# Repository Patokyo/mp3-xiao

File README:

##An mp3 player using a Seeed Studio Xiao Esp32-S3 microcontroller

#Components:
Seeed Studio Xiao Esp32-S3
DAC Decoder with 3.5mm jack - PCM5102A
Micro-SD card reader module
OLED display - 1.5 inch, 128x128, SH1107, 4 pin
Rotary encoder with push button

#--UI--
##Modes:
Playing(folder, mode) - plays songs in the folder using the mode given, e.g. shuffle, straight
Playlist/Album select - option between playlist/album, then displays all the playlists/albums on the sd card

###Playing: mode 0
OLED display - current folder, currently playing song, progress bar, rewind, skip & play controls.
Rotary encoder - Rotate for volume, press to pause, double press to skip, press and rotate back to rewind, press and rotate forward to enter playlist/album select

###Playlist/Album select: mode 1
OLED display - displays folders/files in current directory, e.g. Playlists/Albums to start, then shows all Playlist files or Album folders
Rotary encoder - Rotate to browse folders/files, press to select

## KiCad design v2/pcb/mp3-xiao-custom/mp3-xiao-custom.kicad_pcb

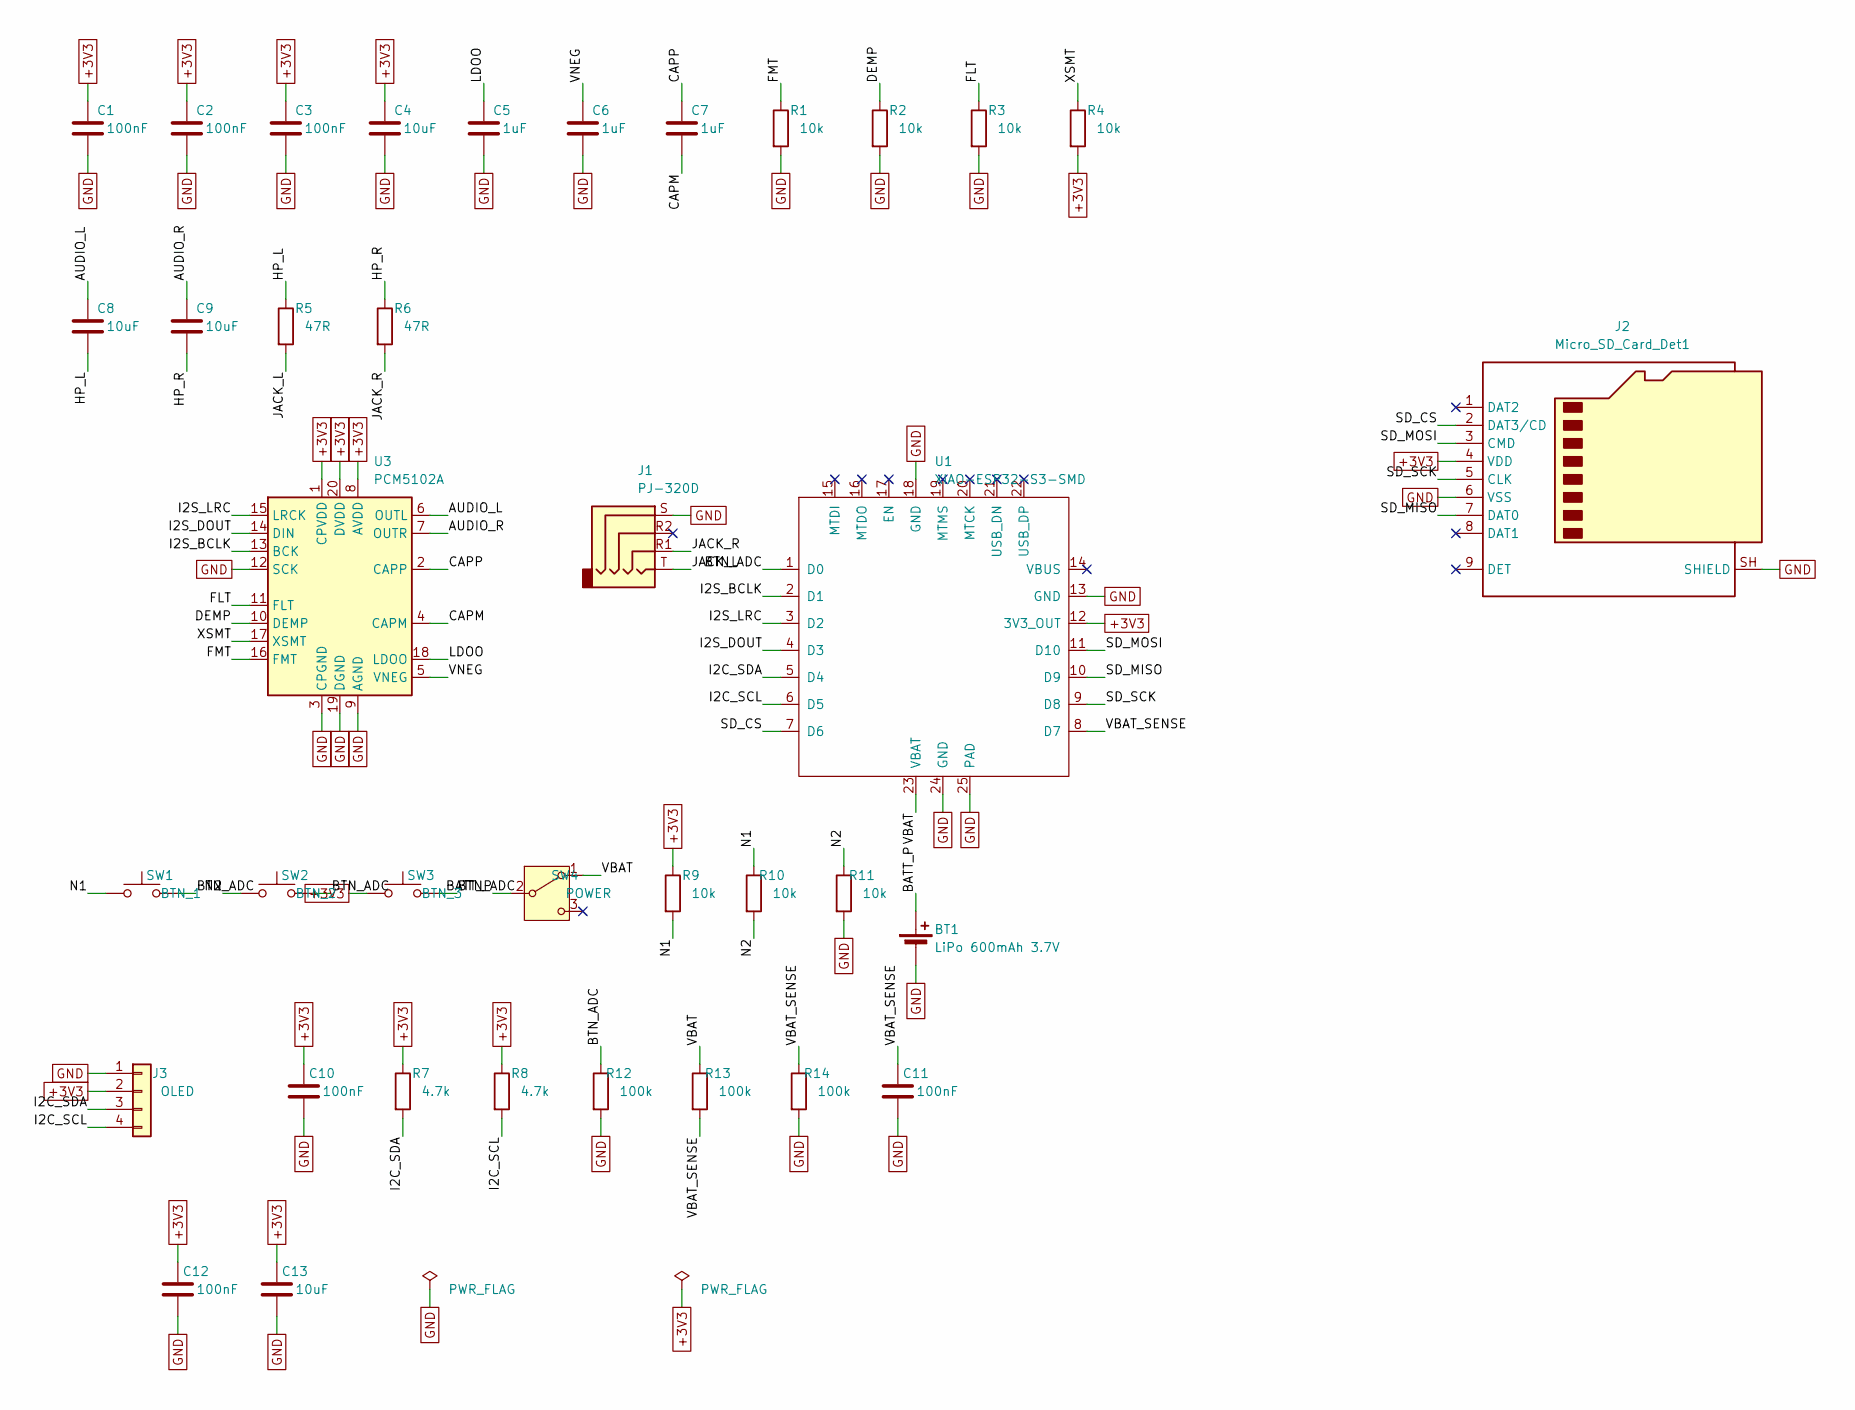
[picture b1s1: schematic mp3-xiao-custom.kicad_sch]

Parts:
BT1: LiPo 600mAh 3.7V; JST_PH_S2B-PH-K_1x02_P2.00mm_Horizontal
C1, C2, C3, C10, C11, C12: 100nF; C_0805_2012Metric_Pad1.18x1.45mm_HandSolder
C4, C8, C9, C13: 10uF; C_0805_2012Metric_Pad1.18x1.45mm_HandSolder
C5, C6, C7: 1uF; C_0805_2012Metric_Pad1.18x1.45mm_HandSolder
J1: PJ-320D; Jack_3.5mm_KoreanHropartsElec_PJ-320D-4A_Horizontal
J2: Micro_SD_Card_Det1; microSD_TF_9P_14.48x13.8mm_SMD
J3: OLED; ER_OLEDM0.91_1x-I2C
R1, R2, R3, R4, R9, R10, R11: 10k; R_0805_2012Metric_Pad1.20x1.40mm_HandSolder
R5, R6: 47R; R_0805_2012Metric_Pad1.20x1.40mm_HandSolder
R7, R8: 4.7k; R_0805_2012Metric_Pad1.20x1.40mm_HandSolder
R12, R13, R14: 100k; R_0805_2012Metric_Pad1.20x1.40mm_HandSolder
SW1: BTN_1; SW_SPST_TL3342
SW2: BTN_2; SW_SPST_TL3342
SW3: BTN_3; SW_SPST_TL3342
SW4: POWER; SW_SPDT_Shouhan_MSK12C02
U1: XIAO-ESP32-S3-SMD
U3: PCM5102A; TSSOP-20_4.4x6.5mm_P0.65mm

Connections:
+3V3: C1.1, C2.1, C3.1, C4.1, C10.1, C12.1, C13.1, J2.4 (VDD), J3.2, R4.2, R7.1, R8.1, R9.1, SW3.1, U1.12 (3V3_OUT), U3.1 (CPVDD), U3.8 (AVDD), U3.20 (DVDD)
/AUDIO_L: C8.1, U3.6 (OUTL)
/AUDIO_R: C9.1, U3.7 (OUTR)
/BATT_P: BT1.1 (+), SW4.2 (B)
/BTN_ADC: R12.1, SW1.2, SW2.2, SW3.2, U1.1 (D0)
/CAPM: C7.2, U3.4 (CAPM)
/CAPP: C7.1, U3.2 (CAPP)
/DEMP: R2.1, U3.10 (DEMP)
/FLT: R3.1, U3.11 (FLT)
/FMT: R1.1, U3.16 (FMT)
/HP_L: C8.2, R5.1
/HP_R: C9.2, R6.1
/I2C_SCL: J3.4, R8.2, U1.6 (D5)
/I2C_SDA: J3.3, R7.2, U1.5 (D4)
/I2S_BCLK: U1.2 (D1), U3.13 (BCK)
/I2S_DOUT: U1.4 (D3), U3.14 (DIN)
/I2S_LRC: U1.3 (D2), U3.15 (LRCK)
/JACK_L: J1.T, R5.2
/JACK_R: J1.R1, R6.2
/LDOO: C5.1, U3.18 (LDOO)
/N1: R9.2, R10.1, SW1.1
/N2: R10.2, R11.1, SW2.1
/SD_CS: J2.2 (DAT3/CD), U1.7 (D6)
/SD_MISO: J2.7 (DAT0), U1.10 (D9)
/SD_MOSI: J2.3 (CMD), U1.11 (D10)
/SD_SCK: J2.5 (CLK), U1.9 (D8)
/VBAT: R13.1, SW4.1 (A), U1.23 (VBAT)
/VBAT_SENSE: C11.1, R13.2, R14.1, U1.8 (D7)
/VNEG: C6.1, U3.5 (VNEG)
/XSMT: R4.1, U3.17 (XSMT)
GND: BT1.2 (-), C1.2, C2.2, C3.2, C4.2, C5.2, C6.2, C10.2, C11.2, C12.2, C13.2, J1.S, J2.6 (VSS), J2.SH (SHIELD), J3.1, R1.2, R2.2, R3.2, R11.2, R12.2, R14.2, U1.13 (GND), U1.18 (GND), U1.24 (GND), U1.25 (PAD), U3.3 (CPGND), U3.9 (AGND), U3.12 (SCK), U3.19 (DGND)

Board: 2 copper layers, 37 parts (1 on the bottom side), 31 nets, no tracks yet.

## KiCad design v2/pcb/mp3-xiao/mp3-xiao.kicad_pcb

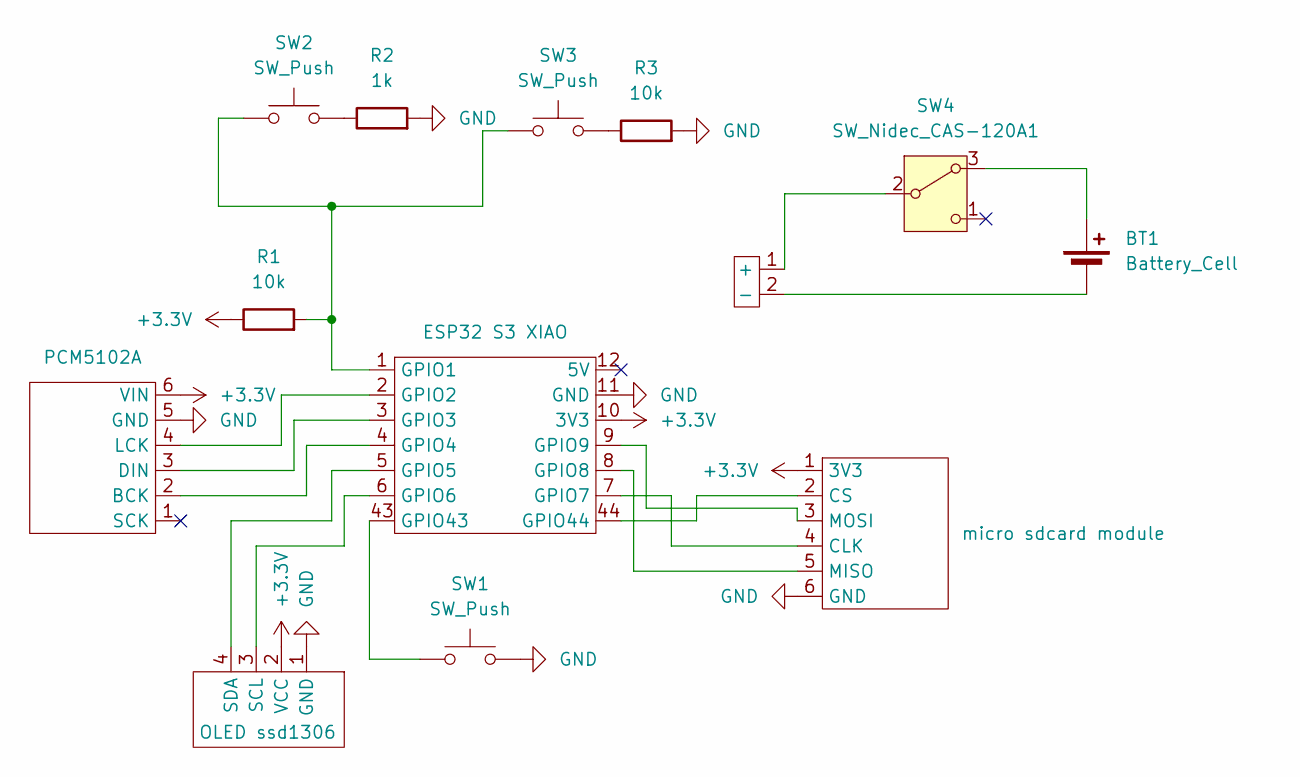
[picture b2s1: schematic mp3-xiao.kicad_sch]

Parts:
BT1: Battery_Cell
R1, R3: 10k; R_0805_2012Metric_Pad1.20x1.40mm_HandSolder
R2: 1k; R_0805_2012Metric_Pad1.20x1.40mm_HandSolder
SW1: SW_Push; SW_PUSH-12mm_Wuerth-430476085716
SW2, SW3: SW_Push; SW_PUSH_6mm
SW4: SW_Nidec_CAS-120A1; spdt slide switch
U1: OLED ssd1306
U2: ESP32 S3 XIAO
U3: micro sdcard module; micro sd card module
U4: PCM5102A
U5: battery_pads

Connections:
+3.3V: R1.1, U1.2 (VCC), U2.10 (3V3), U3.1 (3V3), U4.6 (VIN)
GND: R2.2, R3.2, SW1.2, U1.1 (GND), U2.11 (GND), U3.6 (GND), U4.5 (GND)
unnamed: BT1.1 (+), SW4.3 (A)
unnamed: BT1.2 (-), U5.2 (-)
unnamed: R2.1, SW2.2
unnamed: R3.1, SW3.2
unnamed: SW4.2 (B), U5.1 (+)
unnamed: U1.3 (SCL), U2.6 (GPIO6)
unnamed: U1.4 (SDA), U2.5 (GPIO5)
unnamed: R1.2, SW2.1, SW3.1, U2.1 (GPIO1)
unnamed: U2.2 (GPIO2), U4.4 (LCK)
unnamed: U2.3 (GPIO3), U4.3 (DIN)
unnamed: U2.4 (GPIO4), U4.2 (BCK)
unnamed: U2.7 (GPIO7), U3.4 (CLK)
unnamed: U2.8 (GPIO8), U3.5 (MISO)
unnamed: U2.9 (GPIO9), U3.3 (MOSI)
unnamed: SW1.1, U2.43 (GPIO43)
unnamed: U2.44 (GPIO44), U3.2 (CS)

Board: 2 copper layers, 12 parts (1 on the bottom side), 16 nets, no tracks yet.

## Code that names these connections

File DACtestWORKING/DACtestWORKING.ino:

#include "Arduino.h"
#include "Audio.h"
#include "SPI.h"
#include "SD.h"
#include "FS.h"

// Digital I/O used
#define SD_CS          43
#define SPI_MOSI      9
#define SPI_MISO      8
#define SPI_SCK       7
#define I2S_DOUT      2
#define I2S_BCLK      1
#define I2S_LRC       3

Audio audio;

void my_audio_info(Audio::msg_t m) {
    Serial.printf("%s: %s\n", m.s, m.msg);
}

void setup() {
    Audio::audio_info_callback = my_audio_info;
    pinMode(SD_CS, OUTPUT);
    digitalWrite(SD_CS, HIGH);
    SPI.begin(SPI_SCK, SPI_MISO, SPI_MOSI);
    SPI.setFrequency(1000000);
    Serial.begin(115200);
    SD.begin(SD_CS);
    audio.setPinout(I2S_BCLK, I2S_LRC, I2S_DOUT);
    audio.setVolume(12);
    audio.connecttoFS(SD, "07 Cherub.mp3");
}

void loop(){
    vTaskDelay(1);
    audio.loop();
}

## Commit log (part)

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2025-09-21 added README
2025-09-21 edited README
2025-09-21 Rename README to README.md
2025-09-21 worked on ui
2025-09-22 got DAC working!
2025-09-22 Combined tests into full version
2025-09-22 reworked shuffle
2025-09-23 worked on mp3-xiao
2025-09-23 worked on album selection
2025-09-23 changed one line
2025-09-24 finished album select
2025-09-26 cleaned up ui
2025-09-28 created SSD1306 version
2025-09-30 created 3d model of case
2025-11-02 created final firmware
2025-11-02 changed some icons
2025-11-06 new case proto
2025-11-08 worked on case
2026-03-22 cleaned up files
2026-03-22 began creating v2 pcb
2026-03-22 reorganised files
2026-03-23 worked on v2 pcb
2026-03-25 docs: add XIAO Getting Started link for beginners
    Added Seeed Studio XIAO ESP32-S3 wiki link to help beginners find technical documentation easily.
    Seeed XIAO is an open-source product line.
2026-03-25 docs: add XIAO Getting Started link at first mention only
2026-03-28 Added images
2026-03-28 Added image to README
2026-03-28 added photos to README
2026-03-28 changed image sizes
2026-03-28 fixed image layout
2026-03-28 added more images
2026-03-28 Added UI Showcase to README
2026-03-28 added UI photos
2026-03-28 put hardware components in table
2026-03-28 fixed spelling mistakes
2026-03-28 reorganised README
